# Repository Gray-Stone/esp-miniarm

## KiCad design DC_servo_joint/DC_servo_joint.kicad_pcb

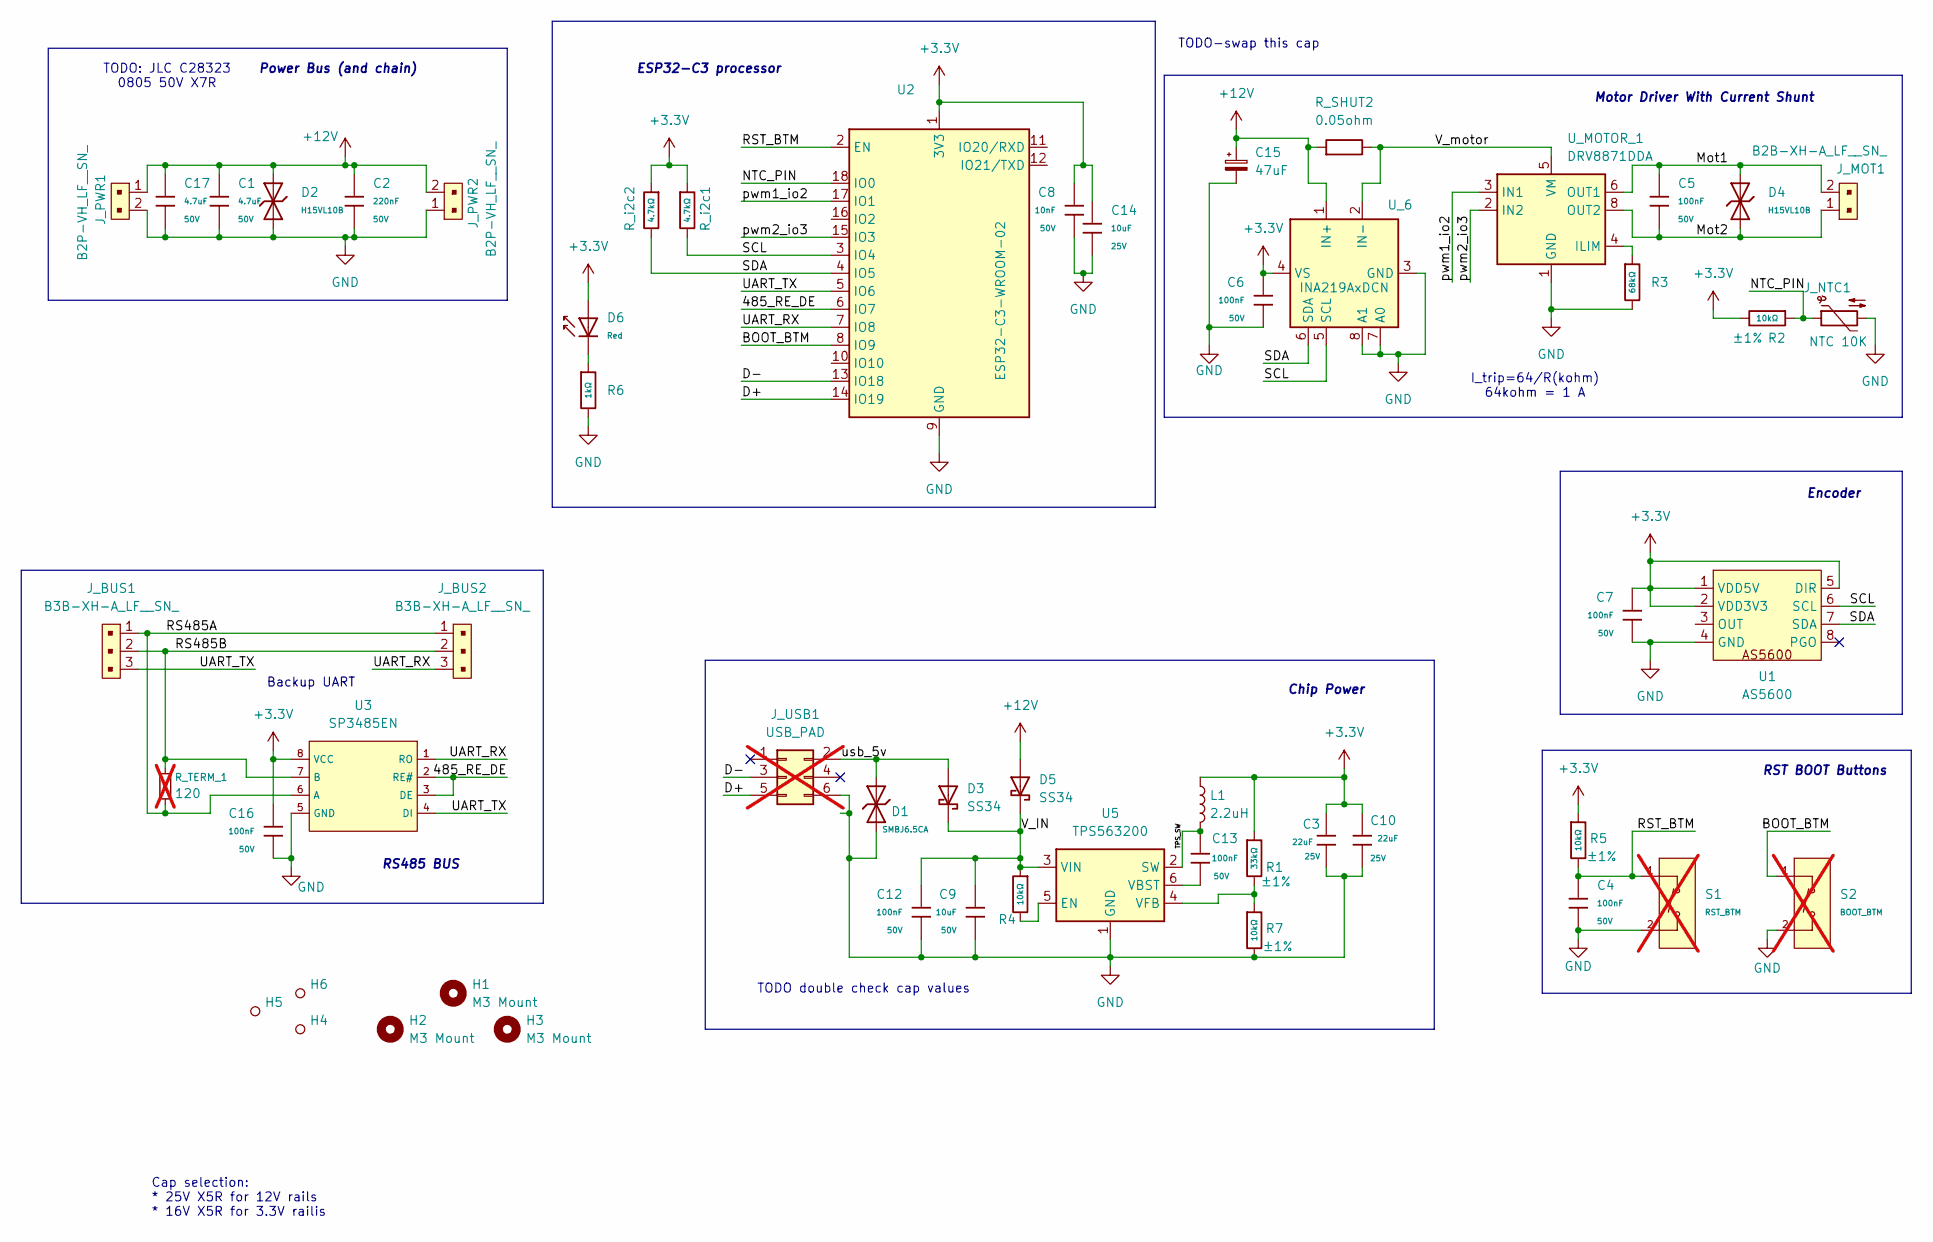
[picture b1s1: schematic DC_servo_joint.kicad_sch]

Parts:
C1, C17: 4.7uF; C_1206; Voltage Rated 50V; Tolerance ±10%; Part 1206B475K500NT; LCSC C29823
C2: 220nF; C_1206; Voltage Rated 50V; Tolerance ±10%; Part 1206B224K500NT; LCSC C1857
C3, C10: 22uF; C_1206; Voltage Rated 25V; Tolerance ±10%; Part CL31A226KAHNNNE; LCSC C12891
C4, C6, C7, C12, C13, C16: 100nF; C_0603; Voltage Rated 50V; Tolerance ±10%; Part CC0603KRX7R9BB104; LCSC C14663
C5: 100nF; C_1206; Voltage Rated 50V; Tolerance ±10%; Part CL31B104KBCNNNC; LCSC C24497
C8: 10nF; C_0603; Voltage Rated 50V; Tolerance ±10%; Part 0603B103K500NT; LCSC C57112
C9: 10uF; C_1206; Voltage Rated 50V; Tolerance ±10%; Part CL31A106KBHNNNE; LCSC C13585
C14: 10uF; C_0805; Voltage Rated 25V; Tolerance ±10%; Part CL21A106KAYNNNE; LCSC C15850
C15: 47uF; CP_Radial_D8.0mm_P3.50mm
D1: SMBJ6.5CA; D_SMB; Breakdown Voltage 7.22V; Part SMBJ6.5CA; LCSC C7420377
D2, D4: H15VL10B; D_DFN1006-2L; Part H15VL10B; LCSC C20615791
D3, D5: SS34; D_SMA; Forward Voltage (Vf@If) 550mV@3A; Reverse Voltage (Vr) 40V; Part SS34; LCSC C8678
D6: Red; D_0603; Part KT-0603R; LCSC C2286
H1, H2, H3: M3 Mount; MountingHole_3.2mm_M3_DIN965
H4, H5, H6: Hole_Tooling_JLCPCB
J_BUS1, J_BUS2: B3B-XH-A_LF__SN_; JST_XH_S3B-XH-A_1x03_P2.50mm_Horizontal; MPN B3B-XH-A(LF)(SN); Digi-Key_PN 455-2248-ND
J_MOT1: B2B-XH-A_LF__SN_; JST_XH_S2B-XH-A_1x02_P2.50mm_Horizontal; MPN B2B-XH-A(LF)(SN); Digi-Key_PN 455-2247-ND
J_NTC1: NTC 10K; JST_XH_S2B-XH-A_1x02_P2.50mm_Horizontal
J_PWR1, J_PWR2: B2P-VH_LF__SN_; JST_VH_S2P-VH_1x02_P3.96mm_Horizontal; MPN B2P-VH(LF)(SN); Digi-Key_PN 455-1639-ND
J_USB1: USB_PAD; PinSocket_2x03_P2.54mm_Vertical; not fitted
L1: 2.2uH; L_Vishay_IHLP-1616; JLC_PART C844973
R1: 33kΩ; R_0402; Overload Voltage (Max) 50V; Tolerance ±1%; Part 0402WGF3302TCE; LCSC C25779
R2, R5, R7: 10kΩ; R_0402; Overload Voltage (Max) 50V; Tolerance ±1%; Part 0402WGF1002TCE; LCSC C25744
R3: 68kΩ; R_0805; Overload Voltage (Max) 150V; Tolerance ±1%; Part 0805W8F6802T5E; LCSC C17801
R4: 10kΩ; R_0603; Overload Voltage (Max) 75V; Tolerance ±1%; Part 0603WAF1002T5E; LCSC C25804
R6: 1kΩ; R_0402; Overload Voltage (Max) 50V; Tolerance ±1%; Part 0402WGF1001TCE; LCSC C11702
R_SHUT2: 0.05ohm; 1206; JLC C7467249
R_TERM_1: 120; 0805; not fitted
R_i2c1, R_i2c2: 4.7kΩ; R_0402; Overload Voltage (Max) 50V; Tolerance ±1%; Part 0402WGF4701TCE; LCSC C25900
S1: RST_BTM; SW_TS-1088-AR02016; Voltage Rating (Dc) 12V; Part TS-1088-AR02016; LCSC C720477; not fitted
S2: BOOT_BTM; SW_TS-1088-AR02016; Voltage Rating (Dc) 12V; Part TS-1088-AR02016; LCSC C720477; not fitted
U1: AS5600; SOIC-8_3.9x4.9mm_P1.27mm; LCSC C499458
U2: ESP32-C3-WROOM-02; LCSC C2934560
U3: SP3485EN; SOIC-8_L5.0-W4.0-P1.27-LS6.0-BL; Supply Voltage 3.3V; Part SP3485EN-L/TR; LCSC C8963
U5: TPS563200; SOT-23-6; LCSC C97253
U_6: INA219AxDCN; SOT-23-8; LCSC C87469
U_MOTOR_1: DRV8871DDA; Texas_HTSOP-8-1EP_3.9x4.9mm_P1.27mm_EP2.95x4.9mm_Mask2.4x3.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; LCSC C75864

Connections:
+3.3V: C3.1, C6.1, C7.1, C8.1, C10.1, C14.1, C16.1, D6.2, L1.1, R1.1, R2.2, R5.1, R_i2c1.1, R_i2c2.1, U1.1 (VDD5V), U1.2 (VDD3V3), U1.5 (DIR), U2.1 (3V3), U3.8 (VCC), U_6.4 (VS)
+12V: C1.1, C2.1, C15.1, C17.1, D2.2, D5.2, J_PWR1.1, J_PWR2.2, R_SHUT2.2, U_6.1 (IN+)
/485_RE_DE: U2.6 (IO7), U3.2 (RE#), U3.3 (DE)
/BOOT_BTM: S2.1 (A), U2.8 (IO9)
/D+: J_USB1.5, U2.14 (IO19)
/D-: J_USB1.3, U2.13 (IO18)
/Mot1: C5.1, D4.2, J_MOT1.2, U_MOTOR_1.6 (OUT1)
/Mot2: C5.2, D4.1, J_MOT1.1, U_MOTOR_1.8 (OUT2)
/NTC_PIN: J_NTC1.1, R2.1, U2.18 (IO0)
/RS485A: J_BUS1.1, J_BUS2.1, R_TERM_1.2, U3.6 (A)
/RS485B: J_BUS1.2, J_BUS2.2, R_TERM_1.1, U3.7 (B)
/RST_BTM: C4.1, R5.2, S1.1 (A), U2.2 (EN)
/SCL: R_i2c1.2, U1.6 (SCL), U2.3 (IO4), U_6.5 (SCL)
/SDA: R_i2c2.2, U1.7 (SDA), U2.4 (IO5), U_6.6 (SDA)
/TPS_SW: C13.1, L1.2, U5.2 (SW)
/UART_RX: J_BUS2.3, U2.7 (IO8), U3.1 (RO)
/UART_TX: J_BUS1.3, U2.5 (IO6), U3.4 (DI)
/V_IN: C9.1, C12.1, D3.1, D5.1, R4.1, U5.3 (VIN)
/V_motor: R_SHUT2.1, U_6.2 (IN-), U_MOTOR_1.5 (VM)
/pwm1_io2: U2.17 (IO1), U_MOTOR_1.3 (IN1)
/pwm2_io3: U2.15 (IO3), U_MOTOR_1.2 (IN2)
/usb_5v: D1.2, D3.2, J_USB1.2
GND: C1.2, C2.2, C3.2, C4.2, C6.2, C7.2, C8.2, C9.2, C10.2, C12.2, C14.2, C15.2, C16.2, C17.2, D1.1, D2.1, J_NTC1.2, J_PWR1.2, J_PWR2.1, J_USB1.6, R3.2, R6.2, R7.2, S1.2 (B), S2.2 (B), U1.4 (GND), U2.9 (GND), U2.19 (GND), U3.5 (GND), U5.1 (GND), U_6.3 (GND), U_6.7 (A0), U_6.8 (A1), U_MOTOR_1.1 (GND), U_MOTOR_1.7 (GND), U_MOTOR_1.9 (GND)
unnamed: D6.1, R6.1
unnamed: R4.2, U5.5 (EN)
unnamed: C13.2, U5.6 (VBST)
unnamed: R1.2, R7.1, U5.4 (VFB)
unnamed: R3.1, U_MOTOR_1.4 (ILIM)

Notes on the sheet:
Power Bus (and chain)
RS485 BUS
TODO-swap this cap
ESP32-C3 processor
Motor Driver With Current Shunt
TODO double check cap values
TODO: JLC C28323 0805 50V X7R
Backup UART
Encoder
Chip Power
I_trip=64/R(kohm) 64kohm = 1 A
RST BOOT Buttons
Cap selection: * 25V X5R for 12V rails * 16V X5R for 3.3V railis

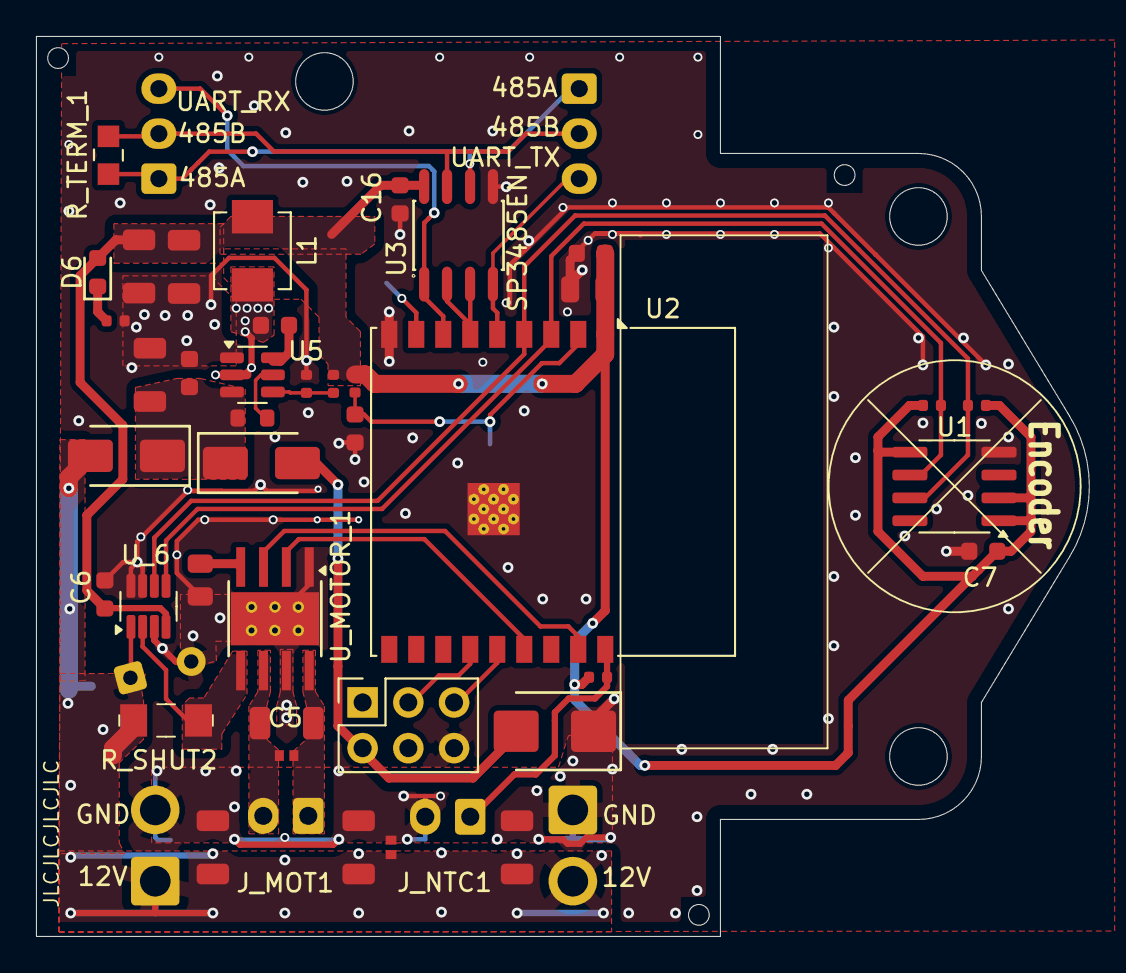
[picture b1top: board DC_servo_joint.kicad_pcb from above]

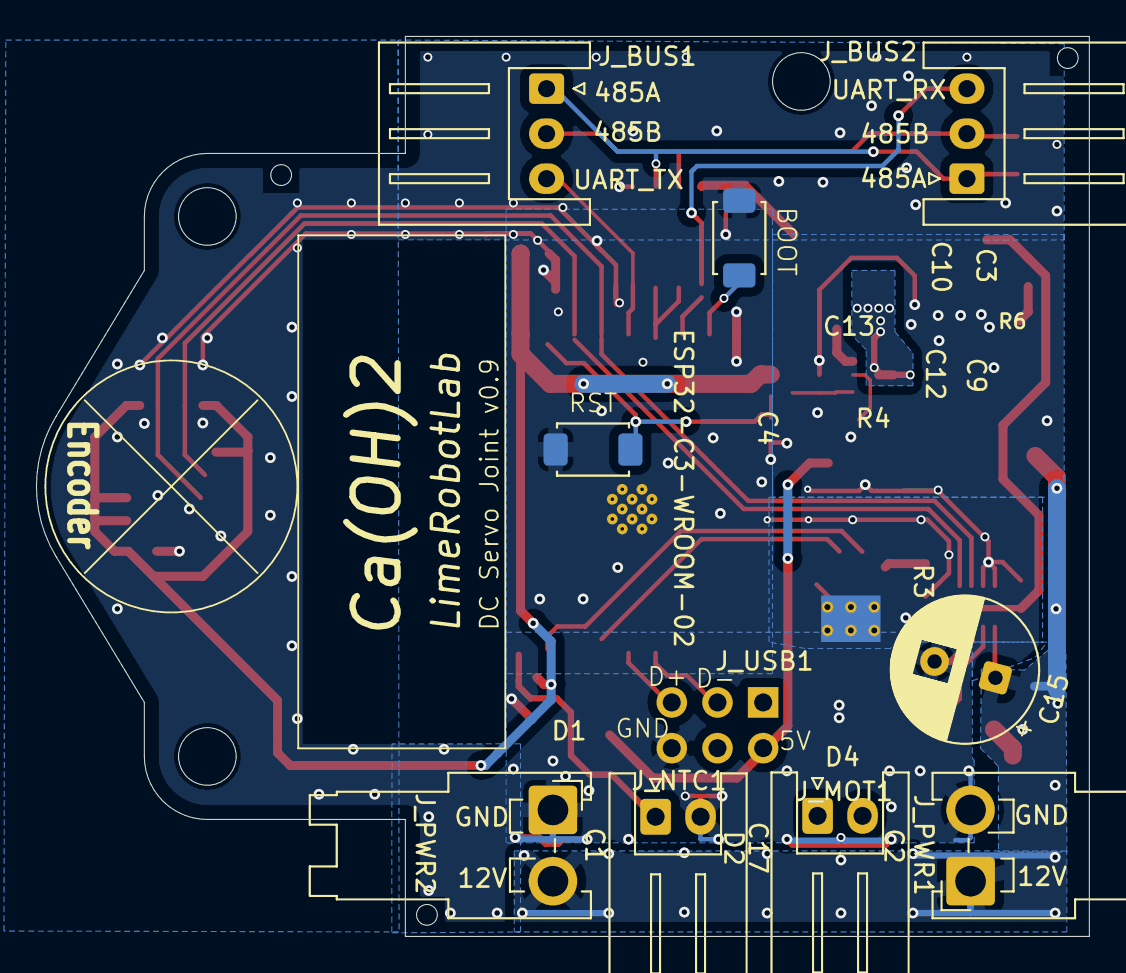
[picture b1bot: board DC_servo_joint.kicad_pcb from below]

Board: 2 copper layers, 58.5 x 50.0 mm, 55 parts (9 on the bottom side), 28 nets.

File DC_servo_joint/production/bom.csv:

Designator,Footprint,Quantity,Value,LCSC Part #
"C1, C17",C_1206,2,4.7uF,C29823
"C10, C3",C_1206,2,22uF,C12891
"C12, C13, C16, C4, C6, C7",C_0603,6,100nF,C14663
C14,C_0805,1,10uF,C15850
C15,CP_Radial_D8.0mm_P3.50mm,1,47uF,
C2,C_1206,1,220nF,C1857
C5,C_1206,1,100nF,C24497
C8,C_0603,1,10nF,C57112
C9,C_1206,1,10uF,C13585
D1,D_SMB,1,SMBJ6.5CA,C7420377
"D2, D4",D_DFN1006-2L,2,H15VL10B,C20615791
"D3, D5",D_SMA,2,SS34,C8678
D6,D_0603,1,Red,C2286
"J_BUS1, J_BUS2",JST_XH_S3B-XH-A_1x03_P2.50mm_Horizontal,2,B3B-XH-A_LF__SN_,B3B-XH-A(LF)(SN)
J_MOT1,JST_XH_S2B-XH-A_1x02_P2.50mm_Horizontal,1,B2B-XH-A_LF__SN_,B2B-XH-A(LF)(SN)
J_NTC1,JST_XH_S2B-XH-A_1x02_P2.50mm_Horizontal,1,NTC 10K,
"J_PWR1, J_PWR2",JST_VH_S2P-VH_1x02_P3.96mm_Horizontal,2,B2P-VH_LF__SN_,B2P-VH(LF)(SN)
J_USB1,PinSocket_2x03_P2.54mm_Vertical,1,USB_PAD,
L1,L_Vishay_IHLP-1616,1,2.2uH,C844973
R1,R_0402,1,33kΩ,C25779
"R2, R5, R7",R_0402,3,10kΩ,C25744
R3,R_0805,1,68kΩ,C17801
R4,R_0603,1,10kΩ,C25804
R6,R_0402,1,1kΩ,C11702
"R_I2C1, R_I2C2",R_0402,2,4.7kΩ,C25900
R_SHUT2,1206,1,0.05ohm,C7467249
R_TERM_1,0805,1,120,
S1,SW_TS-1088-AR02016,1,RST_BTM,C720477
S2,SW_TS-1088-AR02016,1,BOOT_BTM,C720477
U1,SOIC-8_3.9x4.9mm_P1.27mm,1,AS5600,C499458
U2,ESP32-C3-WROOM-02,1,ESP32-C3-WROOM-02,C2934560
U3,SOIC-8_L5.0-W4.0-P1.27-LS6.0-BL,1,SP3485EN,C8963
U5,SOT-23-6,1,TPS563200,C97253
U_6,SOT-23-8,1,INA219AxDCN,C87469
U_MOTOR_1,Texas_HTSOP-8-1EP_3.9x4.9mm_P1.27mm_EP2.95x4.9mm_Mask2.4x3.1mm_ThermalVias,1,DRV8871DDA,C75864

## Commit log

2025-07-31 Start of repo, with git ignore
2025-07-31 Have venv typings package requiremnt setup
2025-07-31 PID kinda working. with build and upload script.
2025-07-31 small clean up and more aggrasive PID values
2025-08-01 Made the single leg UART daisy chain loop worked
2025-08-03 Kicad first round of schematic design done
2025-08-03 Tried to play around with MT6701 encoder. nothing seems to work.
2025-08-03 New Power design with better switching chip.
2025-08-04 Upgraded on power supply design. Simplifyed to no 5V stage, added tvs for protection.
2025-08-04 Change to JST VH connector for power
2025-08-04 Made part selection for all caps and resistors.
2025-08-05 Added a NTP to the system.
2025-08-05 Update the usb header to 8 pins,
2025-08-05 Started Power source layout
2025-08-06 Most layout are in shape
2025-08-06 Finalize button placement
2025-08-07 Finalized Board outline. Fixed I2C signls. Roughtly figured out all compoent's location Still missing 3.3V stuff to be fixed
2025-08-07 Fixed missing tarce, added in some skilscreen fix
2025-08-07 add Kicad ignore
2025-08-07 Fix the 3.3V power layout
2025-08-08 Update Big cap selection. Better layout of power trace. Update silk screen. Fix lots of DRC vialation.
2025-08-08 Add personal Mark to the silkscreen
2025-08-08 Fixed the via size issue. Replace the INA219 with proper part
2025-08-08 Updated the proper value for INA219AxD and did part selection on JLC plugin
2025-08-08 Generated first trial of production file. Also added 2 rotations to parts.
2025-08-09 Add silkscreen in for usb header, Re generated production file
2025-08-09 Redo details caused by ambiguity,Redirect GPIO2
2025-08-09 Move GPIO2 to 3, Clean up I2C trace under encoder.
2025-08-28 Save the final production run of the circuit. mistake on AS5600 pinout
2025-08-28 add note playing on start up
2025-08-28 started work on actual micro python layout. (file created)
2025-09-08 Mark out the error on the DC servo joint PCB
2025-09-10 Adding mDNS feature to the webserver
    streamlined repo structure
2025-12-24 make the build and copy process handle folders.
2025-12-26 add formatting to the repo
2025-12-27 add build script feature for building with node index. each node index generate a separate sub folder in the destination build folder.
2025-12-27 Formatted everything with yapf script.
2025-12-27 Re-arrange folder and putting all code into Firmware section.
